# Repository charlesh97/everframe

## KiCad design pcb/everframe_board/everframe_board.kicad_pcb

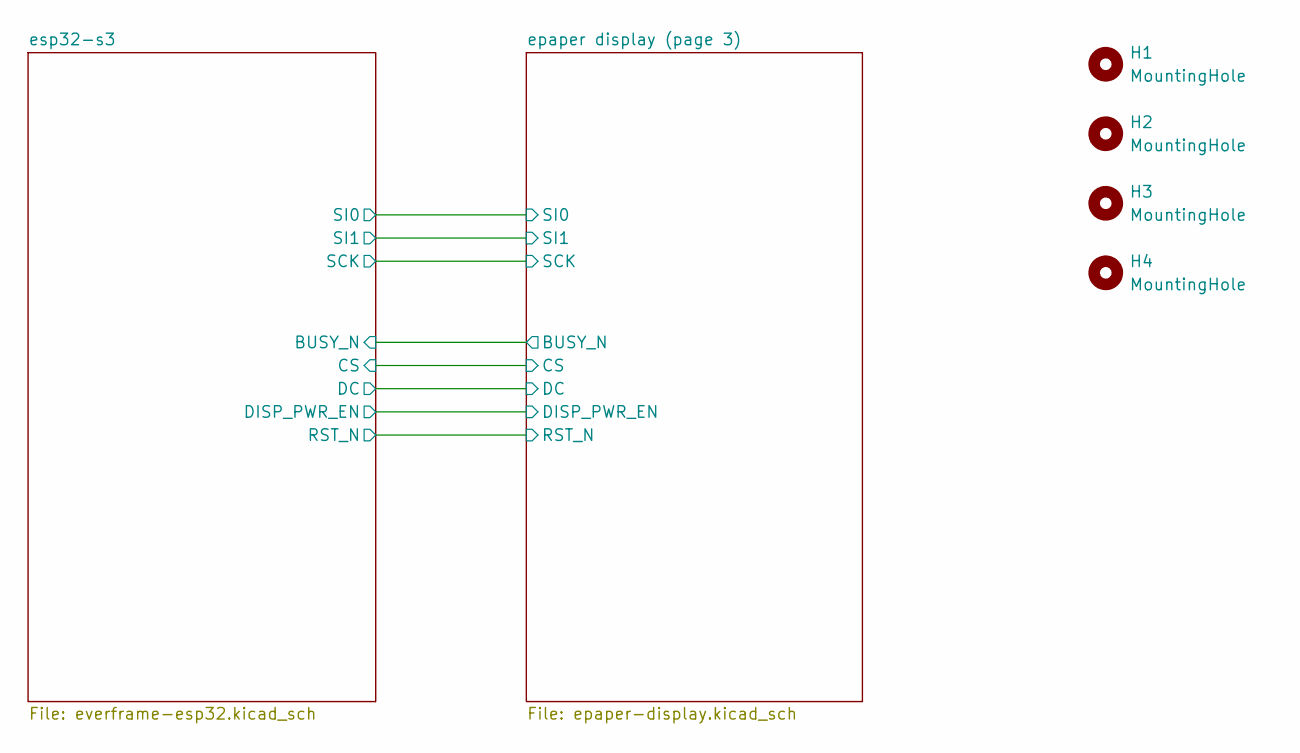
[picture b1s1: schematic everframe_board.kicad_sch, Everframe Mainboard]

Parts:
H1, H2, H3, H4: MountingHole; MountingHole_2mm

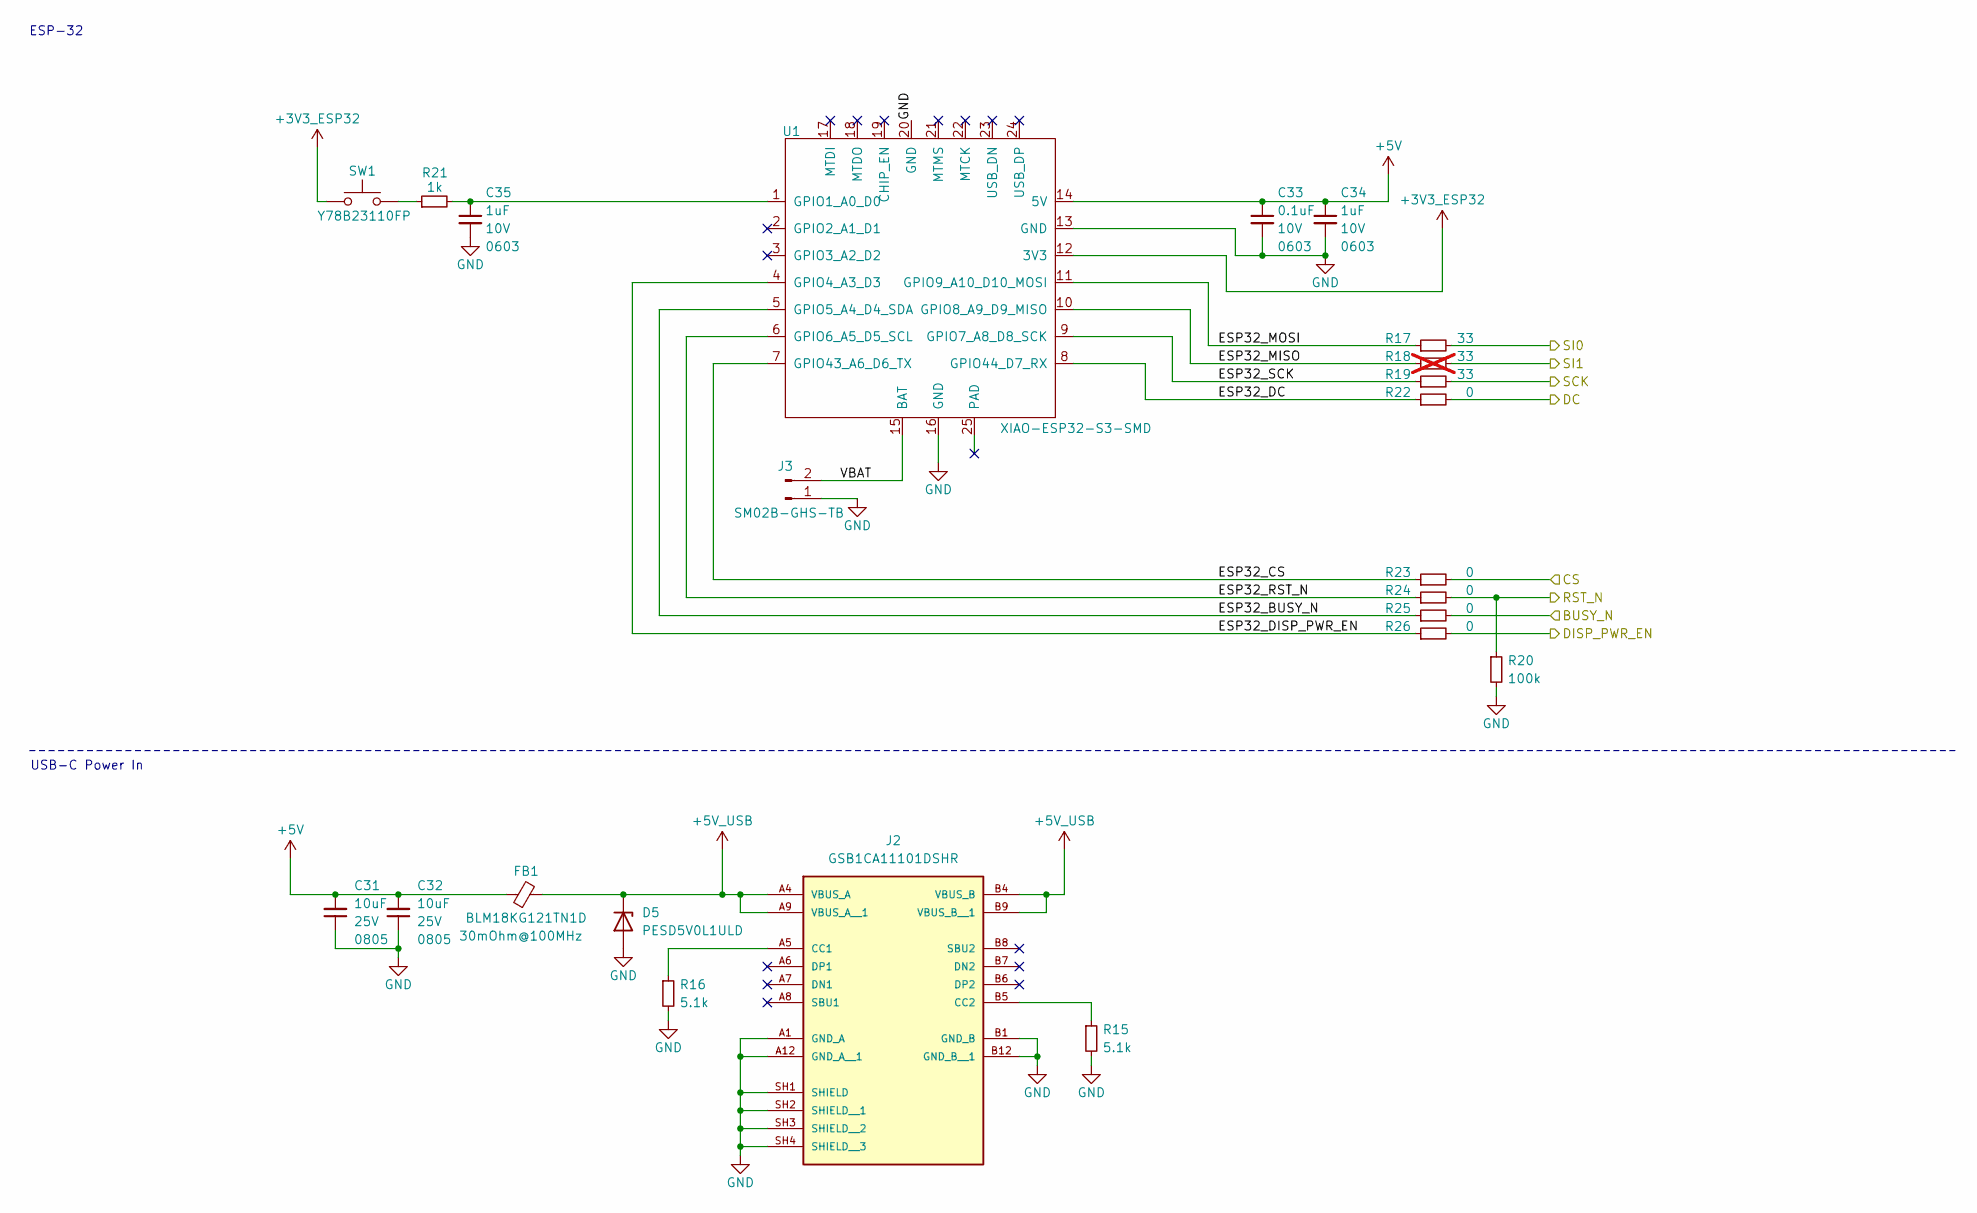
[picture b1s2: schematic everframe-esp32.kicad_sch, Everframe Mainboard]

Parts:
C31, C32: 10uF; C_0805_2012Metric; Voltage 25V
C33: 0.1uF; C_0603_1608Metric; Voltage 10V
C34, C35: 1uF; C_0603_1608Metric; Voltage 10V
D5: PESD5V0L1ULD; D_SOD-882D
FB1: 30mOhm@100MHz; L_0603_1608Metric; Part Number BLM18KG121TN1D
J2: GSB1CA11101DSHR; AMPHENOL_GSB1CA11101DSHR; PARTREV AX1
J3: SM02B-GHS-TB; JST_GH_SM02B-GHS-TB_1x02-1MP_P1.25mm_Horizontal
R15, R16: 5.1k; R_0603_1608Metric
R17, R19: 33; R_0603_1608Metric
R18: 33; R_0603_1608Metric; not fitted
R20: 100k; R_0603_1608Metric
R21: 1k; R_0603_1608Metric
R22, R23, R24, R25, R26: 0; R_0603_1608Metric
SW1: SW_Push; SW_Push_1P1T_NO_CK_KMR2; Part Number Y78B23110FP
U1: XIAO-ESP32-S3-SMD; XIAO-ESP32S3-SMD; MPN 113991114; DigiKey PN 1597-113991114-ND

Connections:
+3V3_ESP32: SW1.1, U1.12 (3V3); also elsewhere on the board
+5V: C31.2, C32.2, C33.1, C34.1, FB1.1, U1.14 (5V)
+5V_USB: D5.1 (K), FB1.2, J2.A4 (VBUS_A), J2.A9 (VBUS_A__1), J2.B4 (VBUS_B), J2.B9 (VBUS_B__1)
/epaper display (page 3)/BUSY_N: R25.2; also elsewhere on the board
/epaper display (page 3)/CS: R23.2; also elsewhere on the board
/epaper display (page 3)/DC: R22.2; also elsewhere on the board
/epaper display (page 3)/DISP_PWR_EN: R26.2; also elsewhere on the board
/epaper display (page 3)/RST_N: R20.1, R24.2; also elsewhere on the board
/epaper display (page 3)/SCK: R19.2; also elsewhere on the board
/epaper display (page 3)/SI0: R17.2; also elsewhere on the board
/epaper display (page 3)/SI1: R18.2; also elsewhere on the board
/esp32-s3/ESP32_BUSY_N: R25.1, U1.5 (GPIO5_A4_D4_SDA)
/esp32-s3/ESP32_CS: R23.1, U1.7 (GPIO43_A6_D6_TX)
/esp32-s3/ESP32_DC: R22.1, U1.8 (GPIO44_D7_RX)
/esp32-s3/ESP32_DISP_PWR_EN: R26.1, U1.4 (GPIO4_A3_D3)
/esp32-s3/ESP32_MISO: R18.1, U1.10 (GPIO8_A9_D9_MISO)
/esp32-s3/ESP32_MOSI: R17.1, U1.11 (GPIO9_A10_D10_MOSI)
/esp32-s3/ESP32_RST_N: R24.1, U1.6 (GPIO6_A5_D5_SCL)
/esp32-s3/ESP32_SCK: R19.1, U1.9 (GPIO7_A8_D8_SCK)
/esp32-s3/VBAT: J3.2, U1.15 (BAT)
GND: C31.1, C32.1, C33.2, C34.2, C35.2, D5.2 (A), J2.A1 (GND_A), J2.A12 (GND_A__1), J2.B1 (GND_B), J2.B12 (GND_B__1), J2.SH1 (SHIELD), J2.SH2 (SHIELD__1), J2.SH3 (SHIELD__2), J2.SH4 (SHIELD__3), J3.1, R15.2, R16.2, R20.2, U1.13 (GND), U1.16 (GND), U1.20 (GND); also elsewhere on the board
unnamed: J2.A5 (CC1), R16.1
unnamed: J2.B5 (CC2), R15.1
unnamed: R21.1, SW1.2
unnamed: C35.1, R21.2, U1.1 (GPIO1_A0_D0)

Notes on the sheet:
USB-C Power In
ESP-32

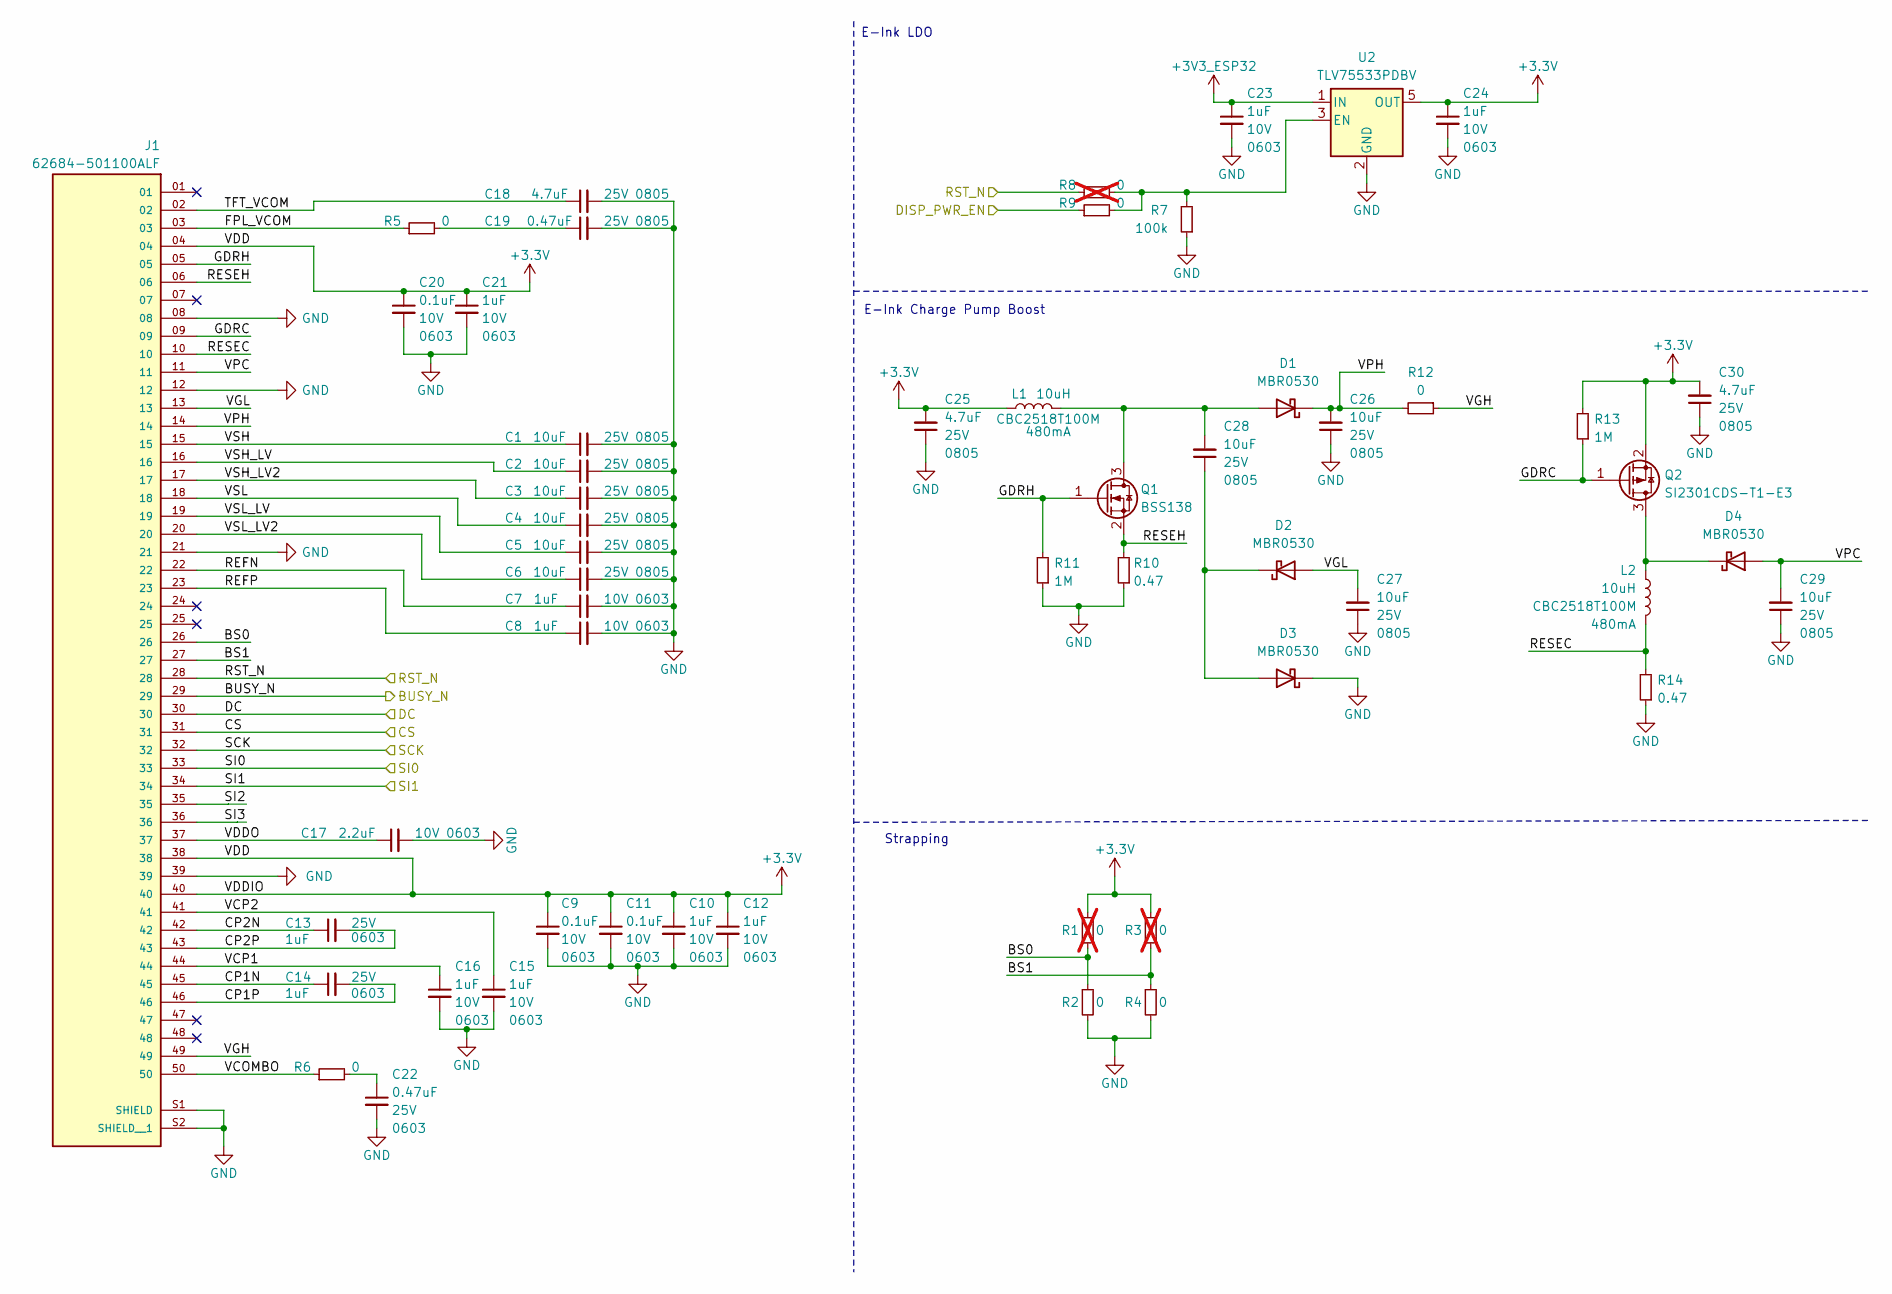
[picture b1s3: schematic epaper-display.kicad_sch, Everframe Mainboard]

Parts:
C1, C2, C3, C4, C5, C6, C26, C27, C28, C29: 10uF; C_0805_2012Metric; Voltage 25V
C7, C8, C10, C12, C15, C16, C21, C23, C24: 1uF; C_0603_1608Metric; Voltage 10V
C9, C11, C20: 0.1uF; C_0603_1608Metric; Voltage 10V
C13, C14: 1uF; C_0603_1608Metric; Voltage 25V
C17: 2.2uF; C_0603_1608Metric; Voltage 10V
C18, C25, C30: 4.7uF; C_0805_2012Metric; Voltage 25V
C19: 0.47uF; C_0805_2012Metric; Voltage 25V
C22: 0.47uF; C_0603_1608Metric; Voltage 25V
D1, D2, D3, D4: MBR0530; D_SOD-123
J1: 62684-501100ALF; AMPHENOL_62684-501100ALF; PARTREV AM
L1, L2: 10uH; L_1008_2520Metric; Part Number CBC2518T100M
Q1: BSS138; SOT-23
Q2: SI2301CDS-T1-E3; SOT-23
R1, R3, R8: 0; R_0603_1608Metric; not fitted
R2, R4, R5, R6, R9, R12: 0; R_0603_1608Metric
R7: 100k; R_0603_1608Metric
R10, R14: 0.47; R_0603_1608Metric
R11, R13: 1M; R_0603_1608Metric
U2: TLV75533PDBV; SOT-23-5; MPN TLV75533PDBVR; DigiKey PN 296-50411-1-ND

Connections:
+3.3V: C9.1, C10.1, C11.1, C12.1, C20.1, C21.1, C24.1, C25.2, C30.2, J1.04, J1.38, J1.40, L1.1, Q2.2 (S), R1.1, R3.1, R13.2, U2.5 (OUT)
+3V3_ESP32: C23.1, U2.1 (IN); also elsewhere on the board
/epaper display (page 3)/BS0: J1.26, R1.2, R2.1
/epaper display (page 3)/BS1: J1.27, R3.2, R4.1
/epaper display (page 3)/BUSY_N: J1.29; also elsewhere on the board
/epaper display (page 3)/CP1N: C14.1, J1.45
/epaper display (page 3)/CP1P: C14.2, J1.46
/epaper display (page 3)/CP2N: C13.1, J1.42
/epaper display (page 3)/CP2P: C13.2, J1.43
/epaper display (page 3)/CS: J1.31; also elsewhere on the board
/epaper display (page 3)/DC: J1.30; also elsewhere on the board
/epaper display (page 3)/DISP_PWR_EN: R9.1; also elsewhere on the board
/epaper display (page 3)/FPL_VCOM: J1.03, R5.1
/epaper display (page 3)/GDRC: J1.09, Q2.1 (G), R13.1
/epaper display (page 3)/GDRH: J1.05, Q1.1 (G), R11.2
/epaper display (page 3)/REFN: C7.1, J1.22
/epaper display (page 3)/REFP: C8.1, J1.23
/epaper display (page 3)/RESEC: J1.10, L2.1, R14.2
/epaper display (page 3)/RESEH: J1.06, Q1.2 (S), R10.2
/epaper display (page 3)/RST_N: J1.28, R8.1; also elsewhere on the board
/epaper display (page 3)/SCK: J1.32; also elsewhere on the board
/epaper display (page 3)/SI0: J1.33; also elsewhere on the board
/epaper display (page 3)/SI1: J1.34; also elsewhere on the board
/epaper display (page 3)/SI2: J1.35
/epaper display (page 3)/SI3: J1.36
/epaper display (page 3)/TFT_VCOM: C18.1, J1.02
/epaper display (page 3)/VCOMBO: J1.50, R6.1
/epaper display (page 3)/VCP1: C16.1, J1.44
/epaper display (page 3)/VCP2: C15.1, J1.41
/epaper display (page 3)/VDDO: C17.1, J1.37
/epaper display (page 3)/VGH: J1.49, R12.1
/epaper display (page 3)/VGL: C27.2, D2.2 (A), J1.13
/epaper display (page 3)/VPC: C29.2, D4.2 (A), J1.11
/epaper display (page 3)/VPH: C26.2, D1.1 (K), J1.14, R12.2
/epaper display (page 3)/VSH: C1.1, J1.15
/epaper display (page 3)/VSH_LV: C2.1, J1.16
/epaper display (page 3)/VSH_LV2: C3.1, J1.17
/epaper display (page 3)/VSL: C4.1, J1.18
/epaper display (page 3)/VSL_LV: C5.1, J1.19
/epaper display (page 3)/VSL_LV2: C6.1, J1.20
GND: C1.2, C2.2, C3.2, C4.2, C5.2, C6.2, C7.2, C8.2, C9.2, C10.2, C11.2, C12.2, C15.2, C16.2, C17.2, C18.2, C19.2, C20.2, C21.2, C22.2, C23.2, C24.2, C25.1, C26.1, C27.1, C29.1, C30.1, D3.1 (K), J1.08, J1.12, J1.21, J1.39, J1.S1 (SHIELD), J1.S2 (SHIELD__1), R2.2, R4.2, R7.1, R10.1, R11.1, R14.1, U2.2 (GND); also elsewhere on the board
unnamed: C19.1, R5.2
unnamed: C22.1, R6.2
unnamed: C28.2, D1.2 (A), L1.2, Q1.3 (D)
unnamed: C28.1, D2.1 (K), D3.2 (A)
unnamed: D4.1 (K), L2.2, Q2.3 (D)
unnamed: R7.2, R8.2, R9.2, U2.3 (EN)

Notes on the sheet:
E-Ink LDO
E-Ink Charge Pump Boost
Strapping

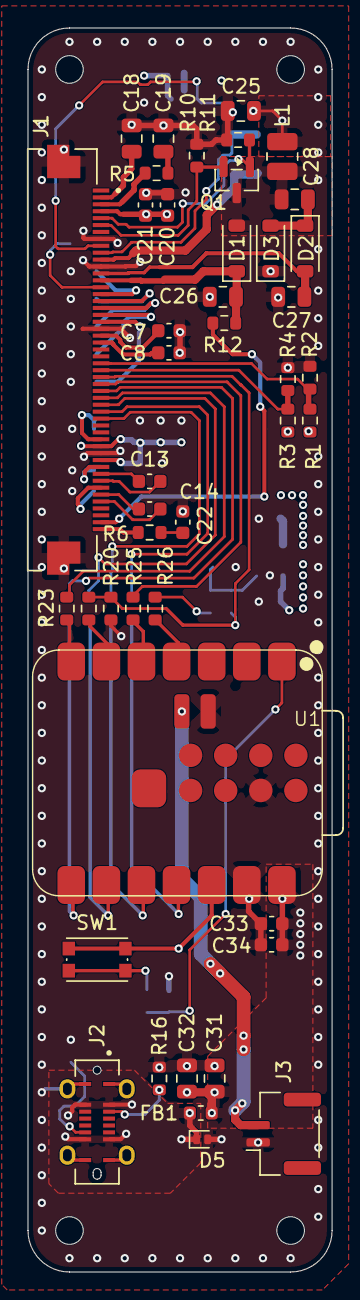
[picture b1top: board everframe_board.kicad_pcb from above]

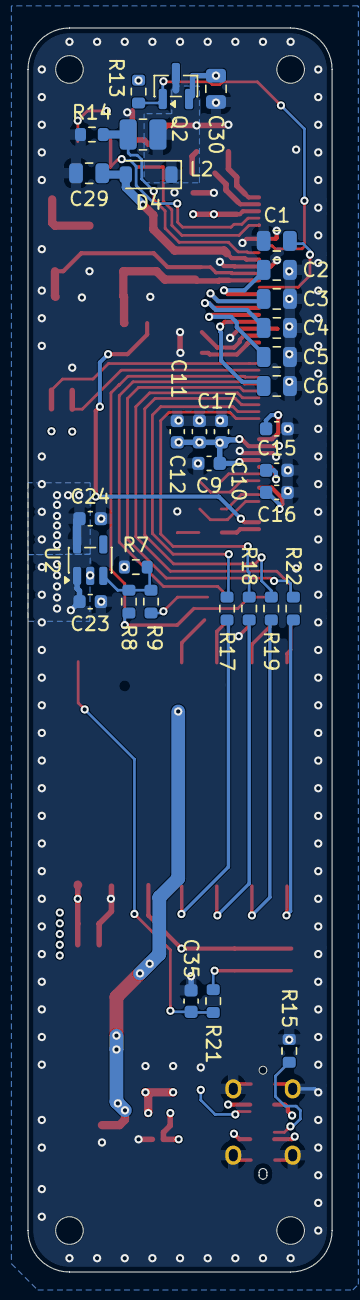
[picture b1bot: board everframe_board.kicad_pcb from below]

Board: 4 copper layers, 22.0 x 90.0 mm, 81 parts (33 on the bottom side), 60 nets.

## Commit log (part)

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2025-10-27 Starting up schematic and board files
2025-11-01 Finished sch, started layout 2L only
2025-11-03 Routed board, mostly need checks
2025-11-18 Update pcb and create packaging design
2025-11-28 Some unused google cloud function code added, esp32 idf embedded project added with display drivers, pcb fab exported
